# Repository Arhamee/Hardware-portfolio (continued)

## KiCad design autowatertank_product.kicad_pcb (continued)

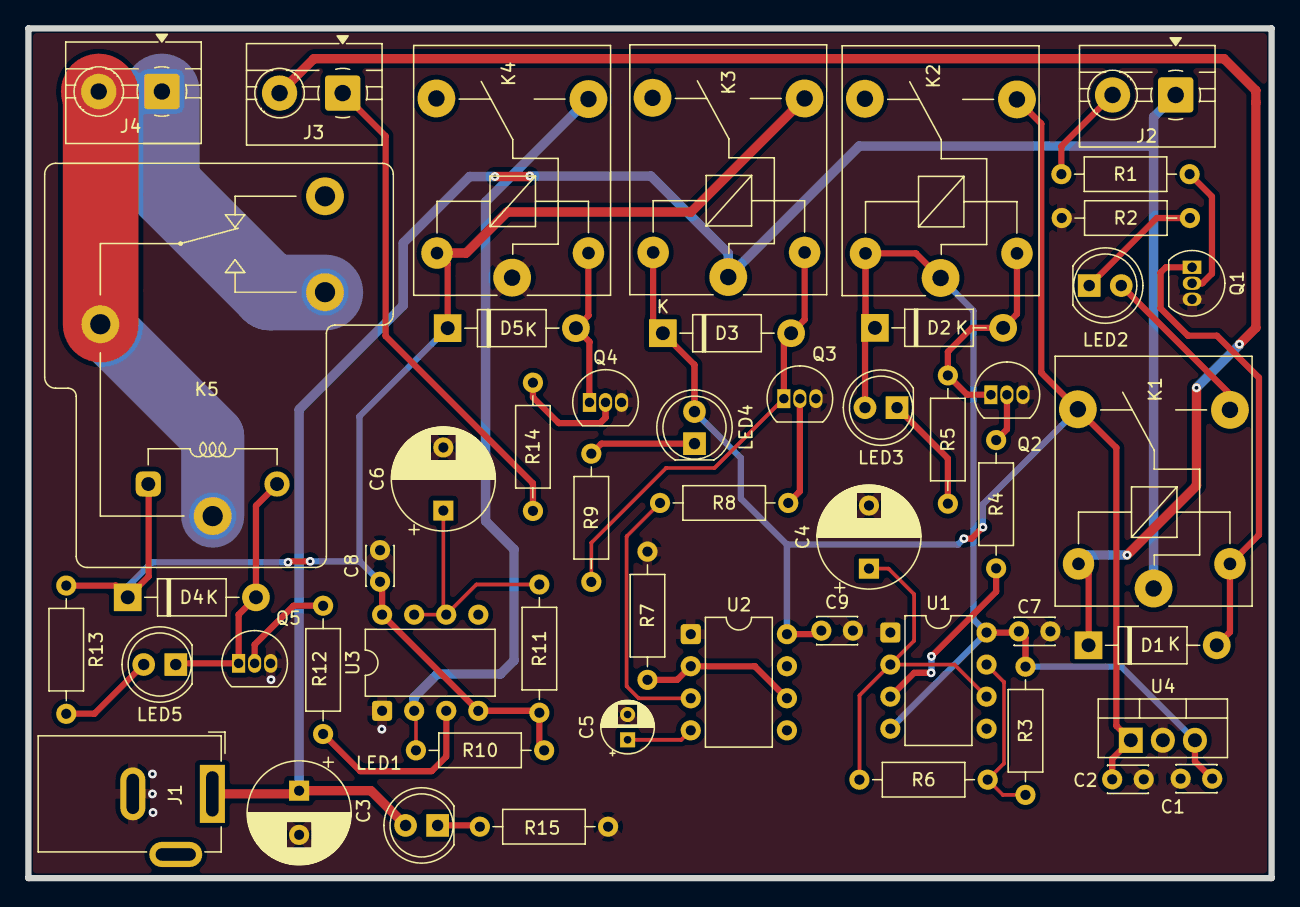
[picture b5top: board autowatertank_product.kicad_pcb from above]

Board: 2 copper layers, 98.5 x 67.3 mm, 52 parts (0 on the bottom side), 35 nets.

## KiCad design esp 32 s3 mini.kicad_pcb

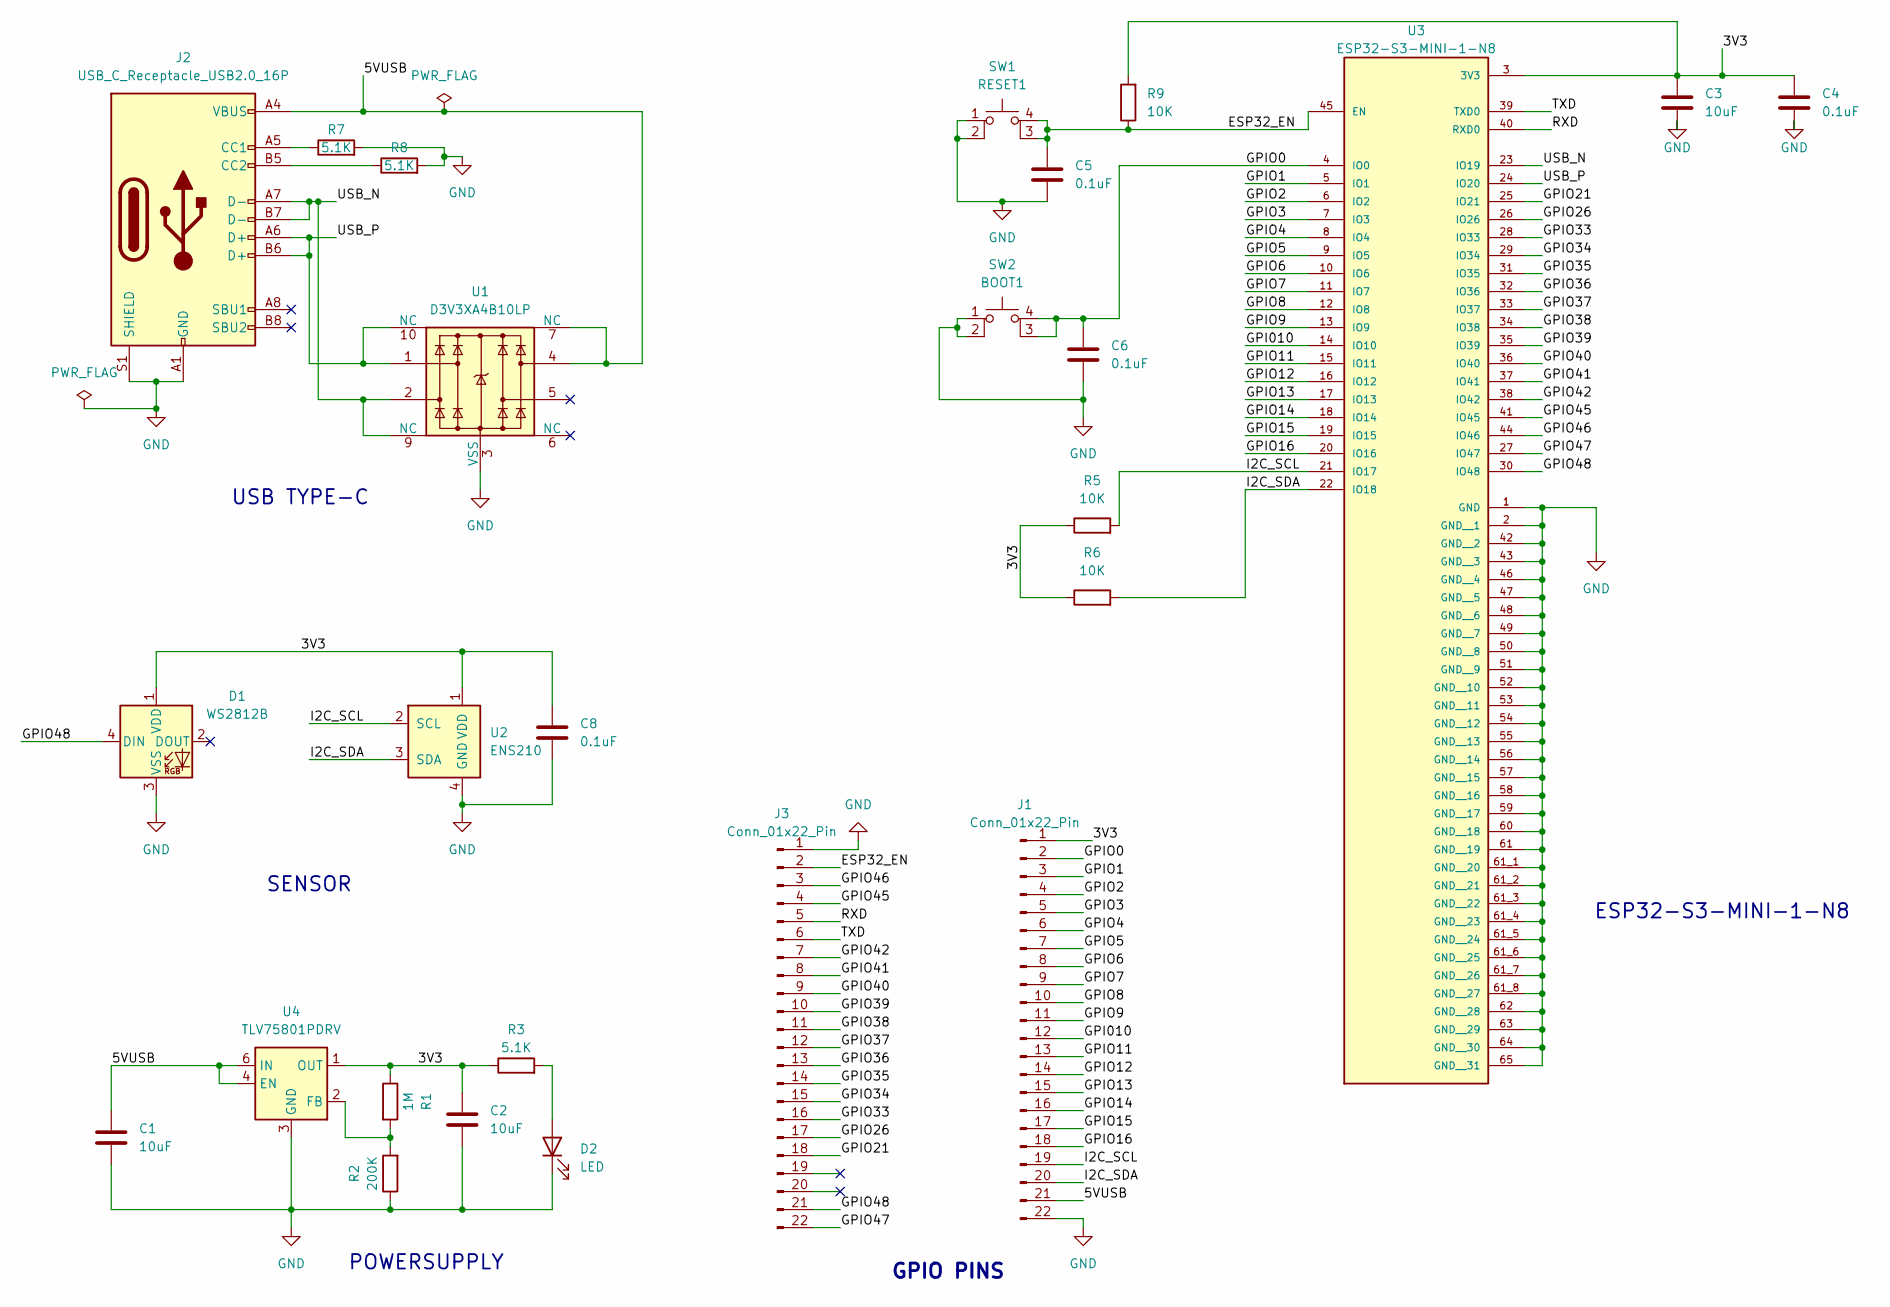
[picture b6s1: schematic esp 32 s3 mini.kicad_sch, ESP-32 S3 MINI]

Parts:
C1, C2, C3: 10uF; C_0603_1608Metric
C4, C5, C6, C8: 0.1uF; C_0603_1608Metric
D1: WS2812B; LED_WS2812B_PLCC4_5.0x5.0mm_P3.2mm
D2: LED; LED_0603_1608Metric
J1, J3: Conn_01x22_Pin; PinHeader_1x22_P2.54mm_Vertical
J2: USB_C_Receptacle_USB2.0_16P; USB_C_Receptacle_GCT_USB4105-xx-A_16P_TopMnt_Horizontal
R1: 1M; R_0603_1608Metric
R2: 200K; R_0603_1608Metric
R3, R7, R8: 5.1K; R_0603_1608Metric
R5, R6, R9: 10K; R_0603_1608Metric
SW1: RESET1; SW_SPST_PTS810
SW2: BOOT1; SW_SPST_PTS810
U1: D3V3XA4B10LP; Diodes_UDFN-10_1.0x2.5mm_P0.5mm
U2: ENS210; AMS_QFN-4-1EP_2x2mm_P0.95mm_EP0.7x1.6mm
U3: ESP32-S3-MINI-1-N8; XCVR_ESP32-S3-MINI-1-N8; PARTREV v0.6
U4: TLV75801PDRV; WSON-6-1EP_2x2mm_P0.65mm_EP1x1.6mm

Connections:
/3V3: C2.1, C3.1, C4.1, C8.1, D1.1 (VDD), J1.1, R1.1, R3.1, R5.1, R6.1, R9.2, U2.1 (VDD), U3.3 (3V3), U4.1 (OUT)
/5VUSB: C1.1, J1.21, J2.A4 (VBUS), J2.A9 (VBUS), J2.B4 (VBUS), J2.B9 (VBUS), U1.4, U1.7 (NC), U4.4 (EN), U4.6 (IN)
/ESP32_EN: C5.1, J3.2, R9.1, SW1.3 (K), SW1.4 (A), U3.45 (EN)
/GPI010: J1.12, U3.14 (IO10)
/GPIO0: C6.1, J1.2, SW2.3 (K), SW2.4 (A), U3.4 (IO0)
/GPIO1: J1.3, U3.5 (IO1)
/GPIO2: J1.4, U3.6 (IO2)
/GPIO3: J1.5, U3.7 (IO3)
/GPIO4: J1.6, U3.8 (IO4)
/GPIO5: J1.7, U3.9 (IO5)
/GPIO6: J1.8, U3.10 (IO6)
/GPIO7: J1.9, U3.11 (IO7)
/GPIO8: J1.10, U3.12 (IO8)
/GPIO9: J1.11, U3.13 (IO9)
/GPIO11: J1.13, U3.15 (IO11)
/GPIO12: J1.14, U3.16 (IO12)
/GPIO13: J1.15, U3.17 (IO13)
/GPIO14: J1.16, U3.18 (IO14)
/GPIO15: J1.17, U3.19 (IO15)
/GPIO16: J1.18, U3.20 (IO16)
/GPIO21: J3.18, U3.25 (IO21)
/GPIO26: J3.17, U3.26 (IO26)
/GPIO33: J3.16, U3.28 (IO33)
/GPIO34: J3.15, U3.29 (IO34)
/GPIO35: J3.14, U3.31 (IO35)
/GPIO36: J3.13, U3.32 (IO36)
/GPIO37: J3.12, U3.33 (IO37)
/GPIO38: J3.11, U3.34 (IO38)
/GPIO39: J3.10, U3.35 (IO39)
/GPIO40: J3.9, U3.36 (IO40)
/GPIO41: J3.8, U3.37 (IO41)
/GPIO42: J3.7, U3.38 (IO42)
/GPIO45: J3.4, U3.41 (IO45)
/GPIO46: J3.3, U3.44 (IO46)
/GPIO47: J3.22, U3.27 (IO47)
/GPIO48: D1.4 (DIN), J3.21, U3.30 (IO48)
/I2C_SCL: J1.19, R5.2, U2.2 (SCL), U3.21 (IO17)
/I2C_SDA: J1.20, R6.2, U2.3 (SDA), U3.22 (IO18)
/RXD: J3.5, U3.40 (RXD0)
/TXD: J3.6, U3.39 (TXD0)
/USB_N: J2.A7 (D-), J2.B7 (D-), U1.2, U1.9 (NC), U3.23 (IO19)
/USB_P: J2.A6 (D+), J2.B6 (D+), U1.1, U1.10 (NC), U3.24 (IO20)
GND: C1.2, C2.2, C3.2, C4.2, C5.2, C6.2, C8.2, D1.3 (VSS), D2.1 (K), J1.22, J2.A1 (GND), J2.A12 (GND), J2.B1 (GND), J2.B12 (GND), J2.S1 (SHIELD), J3.1, R2.1, R7.2, R8.2, SW1.1, SW1.2, SW2.1, SW2.2, U1.3 (VSS), U1.8 (VSS), U2.4 (GND), U2.5 (GND), U3.1 (GND), U3.2 (GND__1), U3.42 (GND__2), U3.43 (GND__3), U3.46 (GND__4), U3.47 (GND__5), U3.48 (GND__6), U3.49 (GND__7), U3.50 (GND__8), U3.51 (GND__9), U3.52 (GND__10), U3.53 (GND__11), U3.54 (GND__12), U3.55 (GND__13), U3.56 (GND__14), U3.57 (GND__15), U3.58 (GND__16), U3.59 (GND__17), U3.60 (GND__18), U3.61 (GND__19), U3.61_1 (GND__20), U3.61_2 (GND__21), U3.61_3 (GND__22), U3.61_4 (GND__23), U3.61_5 (GND__24), U3.61_6 (GND__25), U3.61_7 (GND__26), U3.61_8 (GND__27), U3.62 (GND__28), U3.63 (GND__29), U3.64 (GND__30), U3.65 (GND__31), U4.3 (GND), U4.7 (GND)
unnamed: D2.2 (A), R3.2
unnamed: J2.A5 (CC1), R7.1
unnamed: J2.B5 (CC2), R8.1
unnamed: R1.2, R2.2, U4.2 (FB)

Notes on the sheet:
GPIO PINS
POWERSUPPLY
SENSOR
USB TYPE-C
ESP32-S3-MINI-1-N8

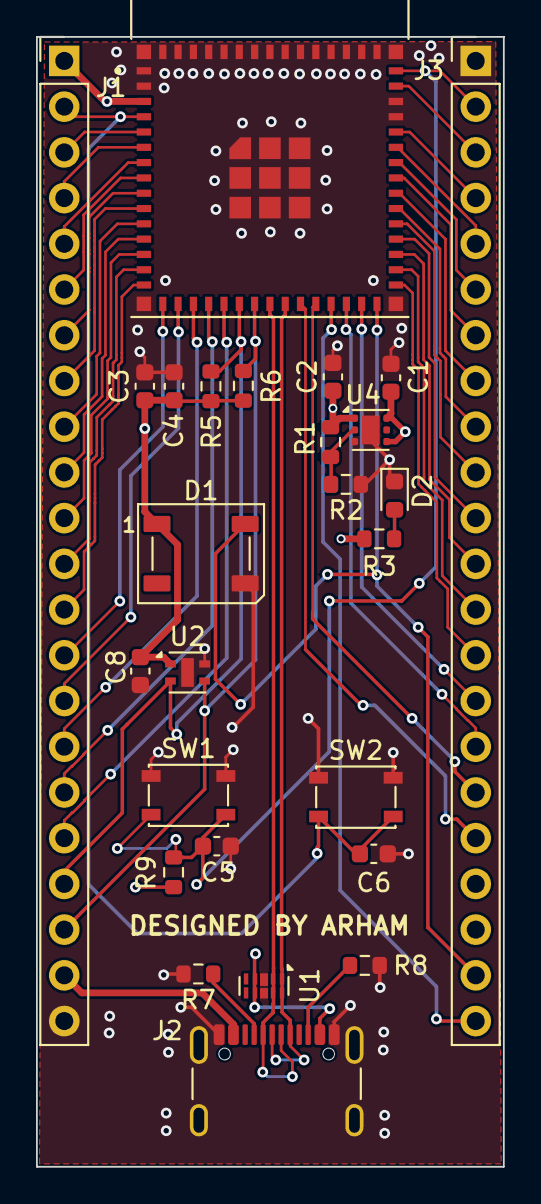
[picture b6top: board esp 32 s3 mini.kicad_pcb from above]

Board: 4 copper layers, 25.9 x 62.8 mm, 26 parts (0 on the bottom side), 47 nets.

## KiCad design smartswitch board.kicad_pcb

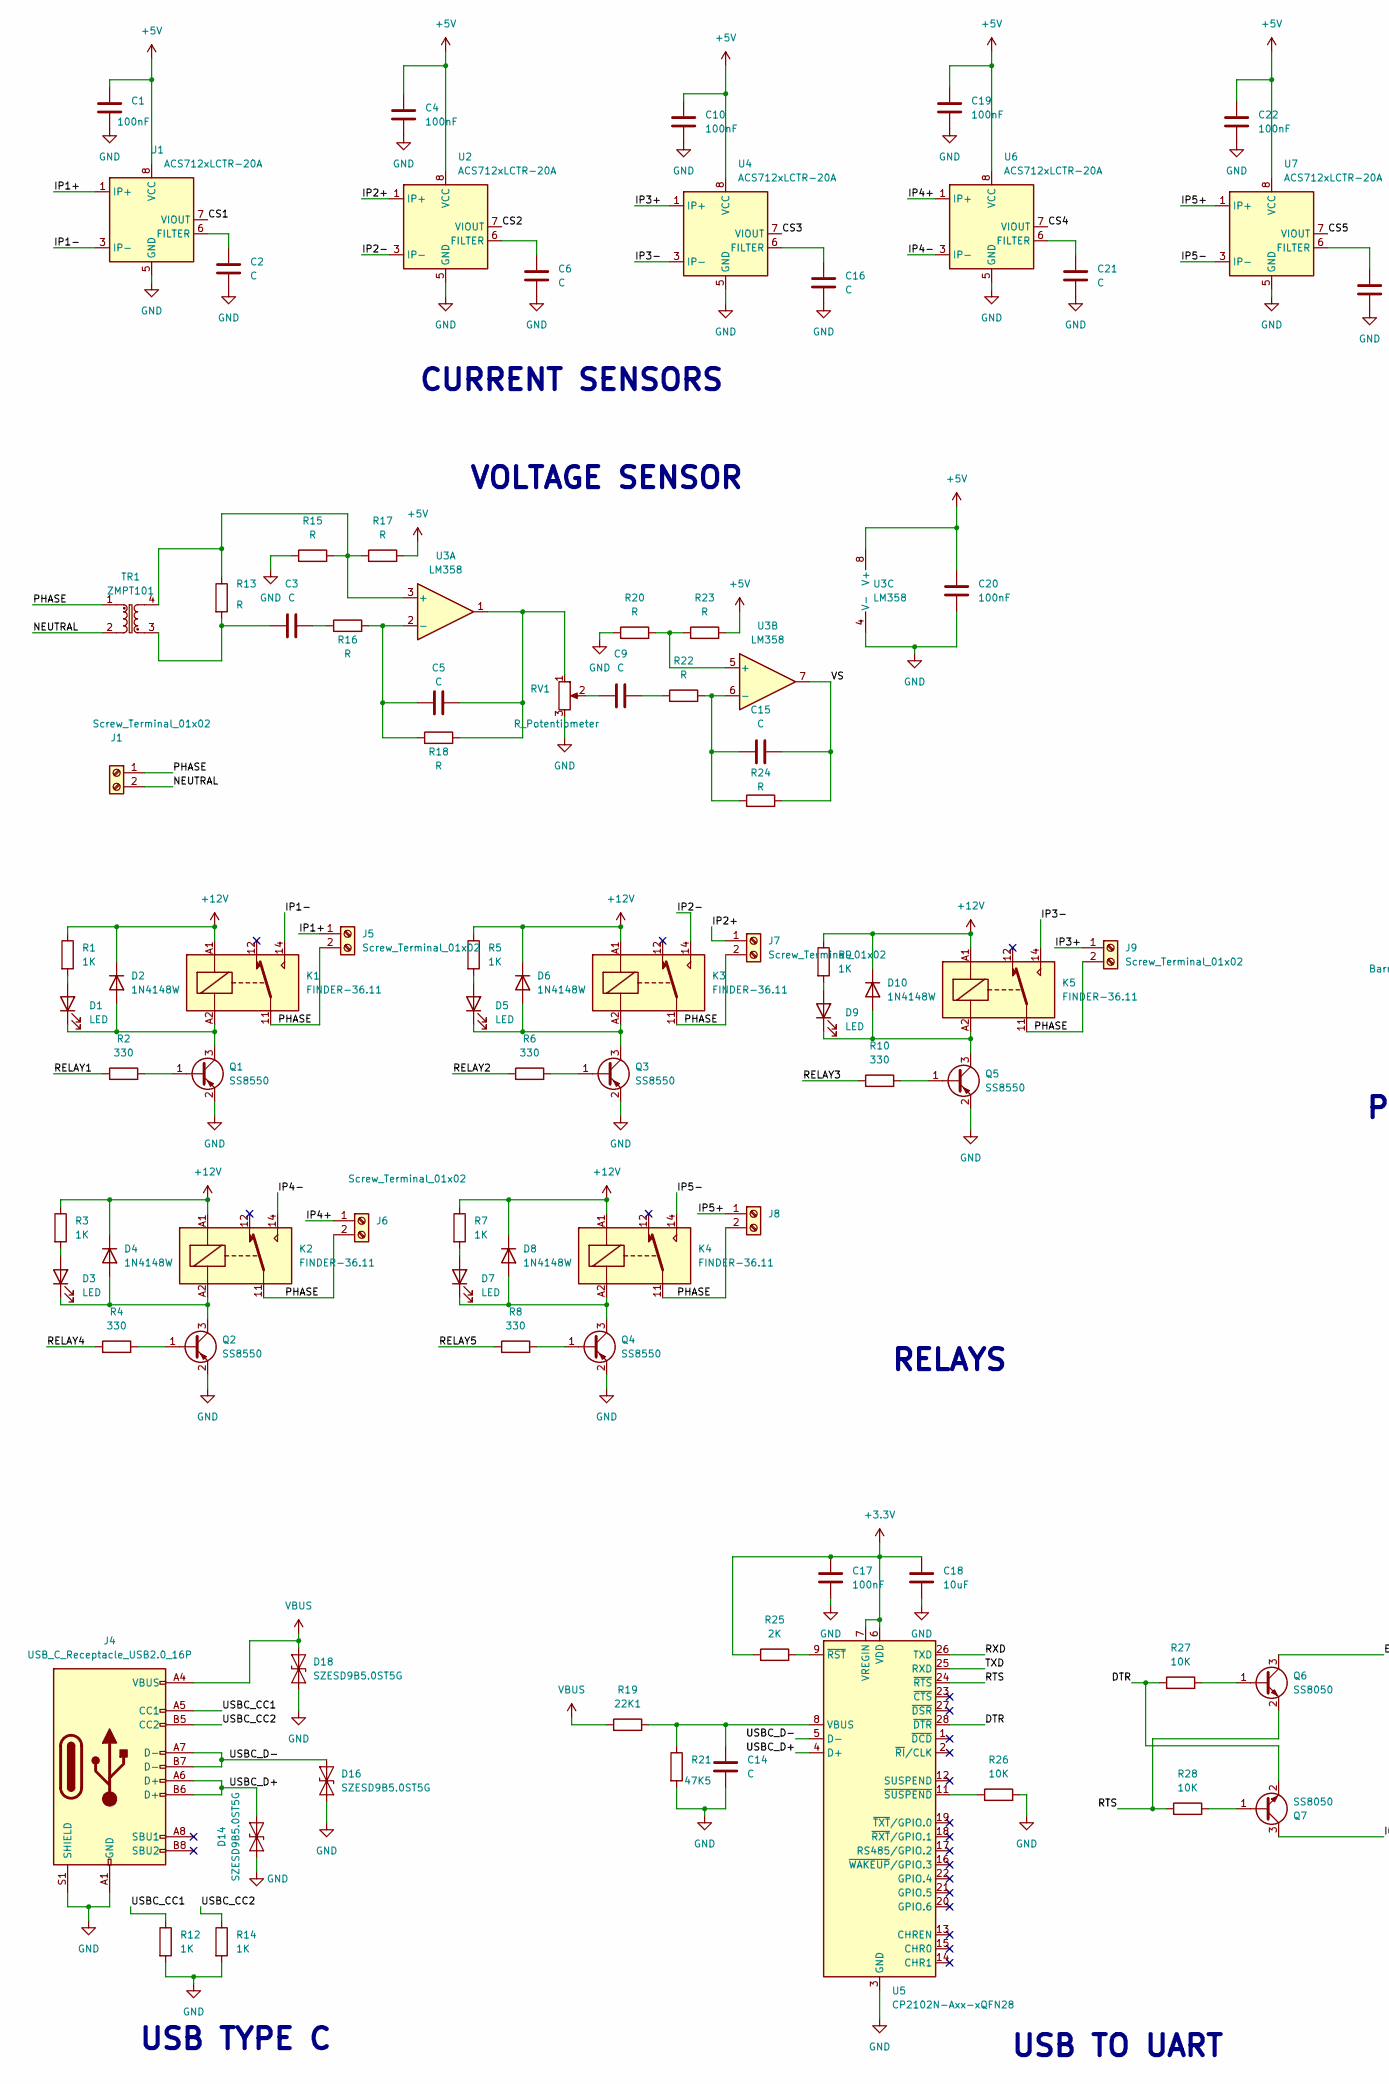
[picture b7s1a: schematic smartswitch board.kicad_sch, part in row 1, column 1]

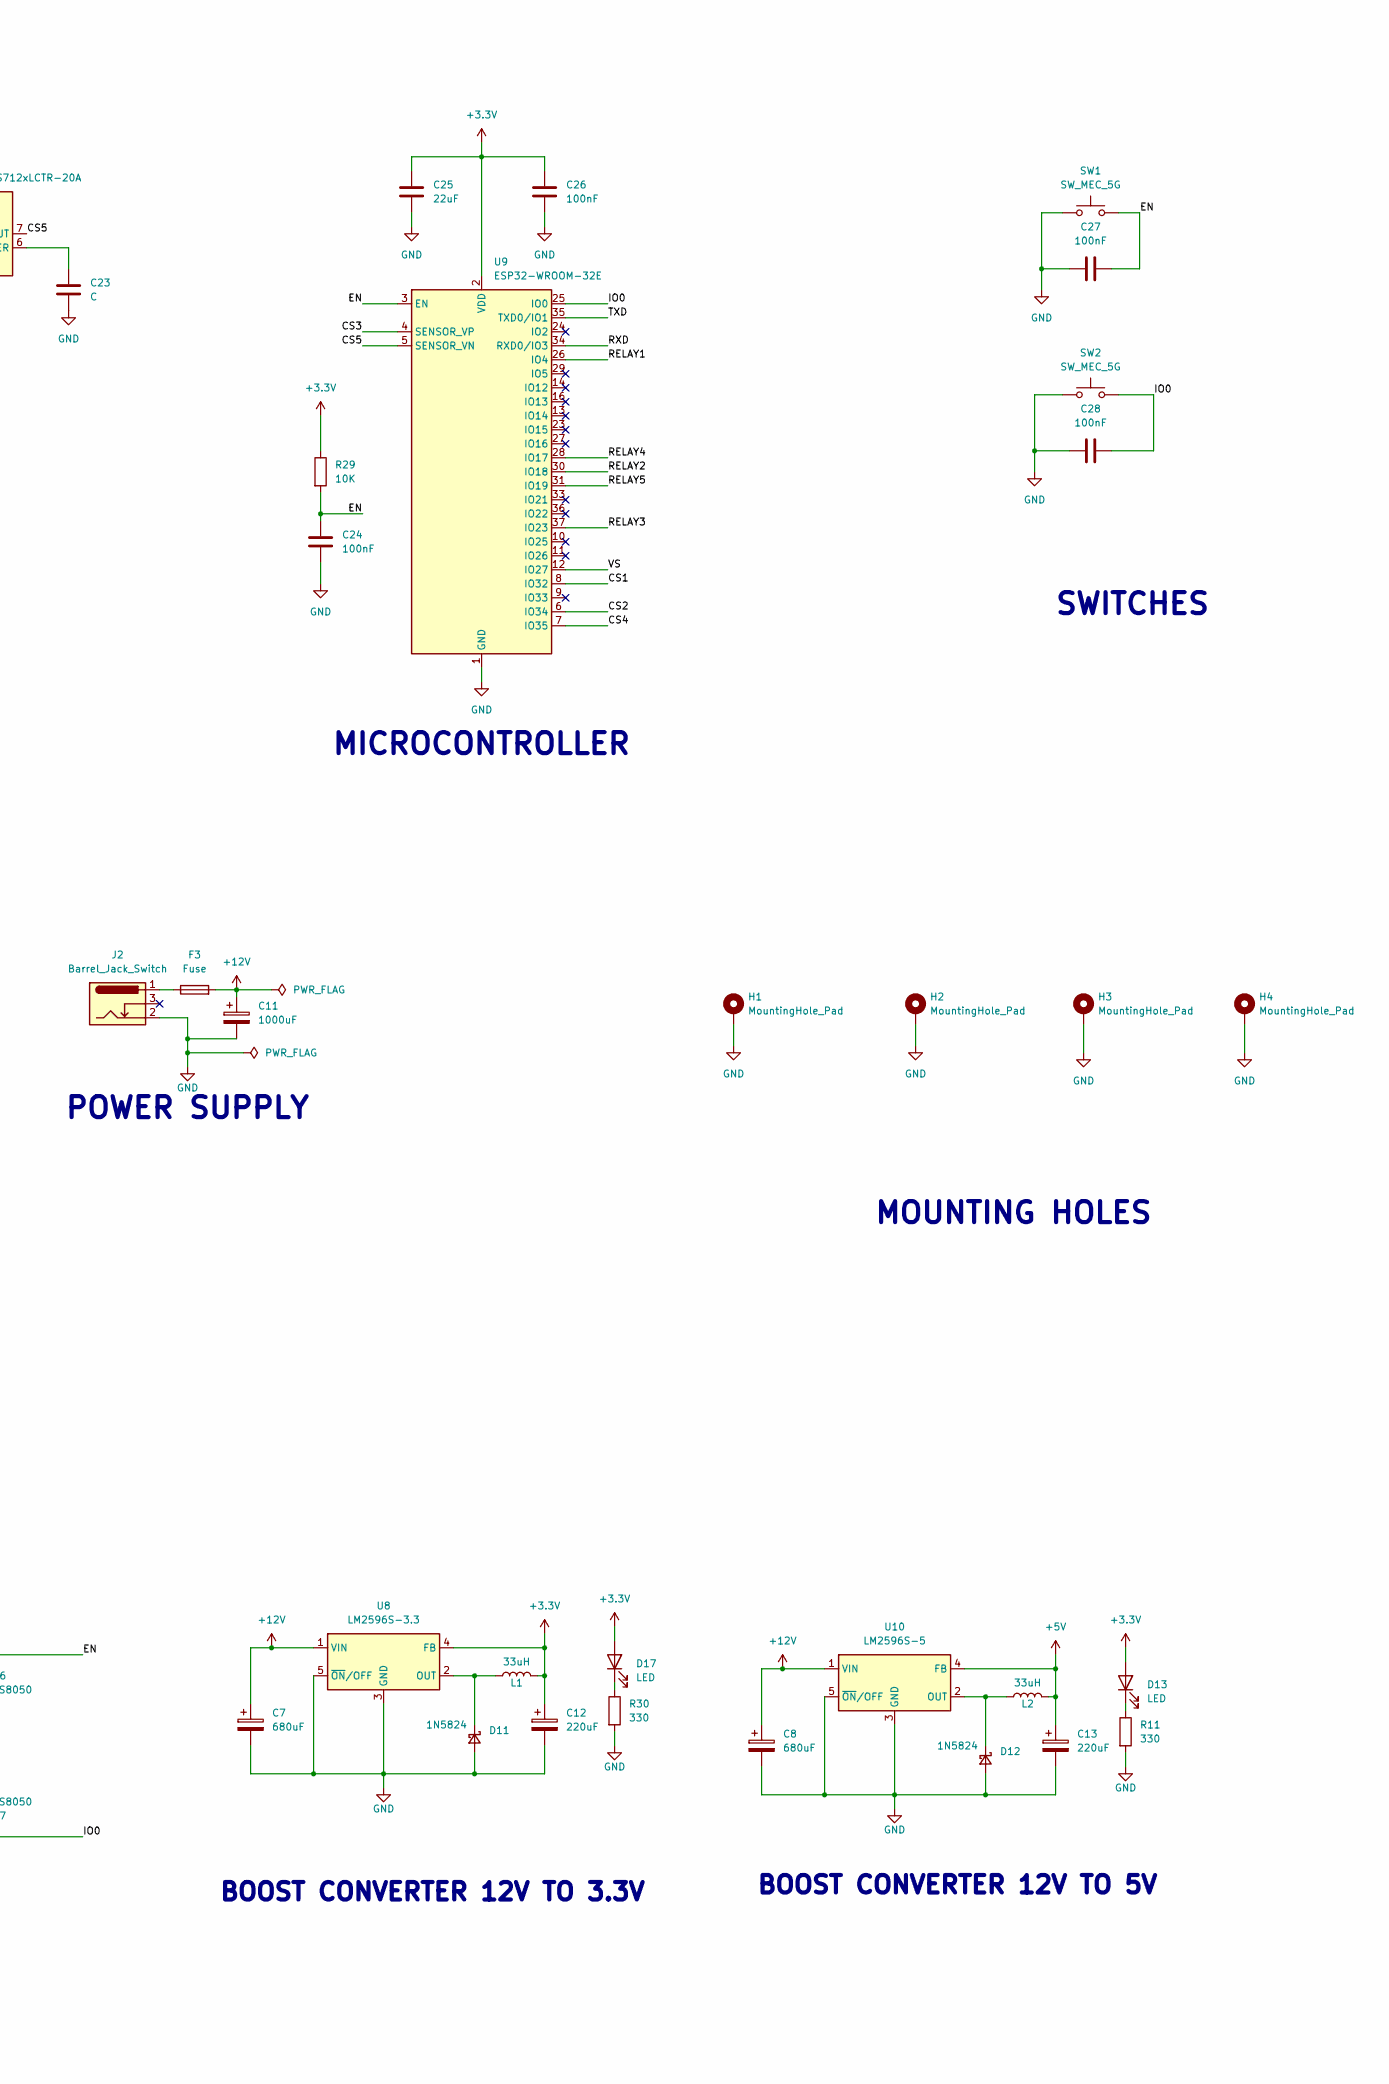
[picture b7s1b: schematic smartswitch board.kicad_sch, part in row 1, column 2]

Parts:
C1, C4, C10, C17, C19, C20, C22, C24, C26, C27, C28: 100nF; C_0402_1005Metric_Pad0.74x0.62mm_HandSolder
C2, C3, C5, C6, C9, C14, C15, C16, C23: C; C_0402_1005Metric_Pad0.74x0.62mm_HandSolder
C7, C8: 680uF; CP_Radial_D7.5mm_P2.50mm
C11: 1000uF; CP_Radial_D8.0mm_P3.50mm
C12, C13: 220uF; CP_Radial_D6.3mm_P2.50mm
C18: 10uF; C_0603_1608Metric_Pad1.08x0.95mm_HandSolder
C21: C; C_0603_1608Metric_Pad1.08x0.95mm_HandSolder
C25: 22uF; C_0603_1608Metric_Pad1.08x0.95mm_HandSolder
D1, D3, D5: LED; C_0402_1005Metric_Pad0.74x0.62mm_HandSolder
D2, D4, D6, D8, D10: 1N4148W; D_SOD-123
D7, D9, D13, D17: LED; LED_0402_1005Metric_Pad0.77x0.64mm_HandSolder
D11, D12: 1N5824; D_0603_1608Metric_Pad1.05x0.95mm_HandSolder
D14, D16, D18: SZESD9B5.0ST5G; D_SOD-923
F3: Fuse; Fuse_1210_3225Metric_Pad1.42x2.65mm_HandSolder
H1, H2, H3, H4: MountingHole_Pad; MountingHole_2.2mm_M2_DIN965_Pad
J1, J5, J6, J7, J8, J9: Screw_Terminal_01x02; TerminalBlock_Phoenix_MKDS-1,5-2_1x02_P5.00mm_Horizontal
J2: Barrel_Jack_Switch; BarrelJack_Horizontal
J4: USB_C_Receptacle_USB2.0_16P; USB_C_Receptacle_GCT_USB4105-xx-A_16P_TopMnt_Horizontal
K1, K2, K3, K4, K5: FINDER-36.11; Relay_SPDT_Finder_36.11
L1, L2: 33uH; L_Changjiang_FNR4015S
Q1, Q2, Q3, Q4, Q5: SS8550; SOT-23
Q6, Q7: SS8050; SOT-23
R1, R3, R5, R7, R9, R12, R14: 1K; R_0603_1608Metric_Pad0.98x0.95mm_HandSolder
R2, R4, R6, R8, R10, R11, R30: 330; R_0603_1608Metric_Pad0.98x0.95mm_HandSolder
R13, R15, R16, R17, R18, R20, R22, R23, R24: R; R_0603_1608Metric_Pad0.98x0.95mm_HandSolder
R19: 22K1; R_0603_1608Metric_Pad0.98x0.95mm_HandSolder
R21: 47K5; R_0603_1608Metric_Pad0.98x0.95mm_HandSolder
R25: 2K; R_0603_1608Metric_Pad0.98x0.95mm_HandSolder
R26, R27, R28, R29: 10K; R_0603_1608Metric_Pad0.98x0.95mm_HandSolder
RV1: R_Potentiometer; Potentiometer_Bourns_3296W_Vertical
SW1, SW2: SW_MEC_5G; PTS645S_SMTR92_CNK
TR1: ZMPT101; Transformer_Zeming_ZMPT101K
U1, U2, U4, U6, U7: ACS712xLCTR-20A; SOIC-8_3.9x4.9mm_P1.27mm
U3: LM358; SOIC-8_3.9x4.9mm_P1.27mm
U5: CP2102N-Axx-xQFN28; QFN-28-1EP_5x5mm_P0.5mm_EP3.35x3.35mm
U8: LM2596S-3.3; TO-263-5_TabPin3
U9: ESP32-WROOM-32E; ESP32-WROOM-32D
U10: LM2596S-5; TO-263-5_TabPin3

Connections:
+3.3V: C12.1, C17.1, C18.1, C25.1, C26.1, D13.2 (A), D17.2 (A), L1.2, R25.1, R29.1, U5.6 (VDD), U5.7 (VREGIN), U8.4 (FB), U9.2 (VDD)
+5V: C1.1, C4.1, C10.1, C13.1, C19.1, C20.2, C22.1, L2.2, R17.2, R23.2, U1.8 (VCC), U2.8 (VCC), U3.8 (V+), U4.8 (VCC), U6.8 (VCC), U7.8 (VCC), U10.4 (FB)
+12V: C7.1, C8.1, C11.1, D2.1 (K), D4.1 (K), D6.1 (K), D8.1 (K), D10.1 (K), F3.2, K1.A1, K2.A1, K3.A1, K4.A1, K5.A1, R1.1, R3.1, R5.1, R7.1, R9.1, U8.1 (VIN), U10.1 (VIN)
/CS1: U1.7 (VIOUT), U9.8 (IO32)
/CS2: U2.7 (VIOUT), U9.6 (IO34)
/CS3: U4.7 (VIOUT), U9.4 (SENSOR_VP)
/CS4: U6.7 (VIOUT), U9.7 (IO35)
/CS5: U7.7 (VIOUT), U9.5 (SENSOR_VN)
/DTR: Q7.2 (E), R27.1, U5.28 (~DTR)
/EN: C24.1, C27.1, Q6.3 (C), R29.2, SW1.3 (B), SW1.4 (B), U9.3 (EN)
/IO0: C28.2, Q7.3 (C), SW2.3 (B), SW2.4 (B), U9.25 (IO0)
/IP1+: J5.1, U1.1 (IP+), U1.2 (IP+)
/IP1-: K1.14, U1.3 (IP-), U1.4 (IP-)
/IP2+: J7.1, U2.1 (IP+), U2.2 (IP+)
/IP2-: K3.14, U2.3 (IP-), U2.4 (IP-)
/IP3+: J9.1, U4.1 (IP+), U4.2 (IP+)
/IP3-: K5.14, U4.3 (IP-), U4.4 (IP-)
/IP4+: J6.1, U6.1 (IP+), U6.2 (IP+)
/IP4-: K2.14, U6.3 (IP-), U6.4 (IP-)
/IP5+: J8.1, U7.1 (IP+), U7.2 (IP+)
/IP5-: K4.14, U7.3 (IP-), U7.4 (IP-)
/NEUTRAL: J1.2, TR1.2
/PHASE: J1.1, J5.2, J6.2, J7.2, J8.2, J9.2, K1.11, K2.11, K3.11, K4.11, K5.11, TR1.1
/RELAY1: R2.1, U9.26 (IO4)
/RELAY2: R6.1, U9.30 (IO18)
/RELAY3: R10.1, U9.37 (IO23)
/RELAY4: R4.1, U9.28 (IO17)
/RELAY5: R8.1, U9.31 (IO19)
/RTS: Q6.2 (E), R28.1, U5.24 (~RTS)
/RXD: U5.26 (TXD), U9.34 (RXD0/IO3)
/TXD: U5.25 (RXD), U9.35 (TXD0/IO1)
/USBC_CC1: J4.A5 (CC1), R12.1
/USBC_CC2: J4.B5 (CC2), R14.1
/USBC_D+: D14.2 (A2), J4.A6 (D+), J4.B6 (D+), U5.4 (D+)
/USBC_D-: D16.2 (A2), J4.A7 (D-), J4.B7 (D-), U5.5 (D-)
/VS: C15.2, R24.2, U3.7, U9.12 (IO27)
GND: C1.2, C2.2, C4.2, C6.2, C7.2, C8.2, C10.2, C11.2, C12.2, C13.2, C14.2, C16.2, C17.2, C18.2, C19.2, C20.1, C21.2, C22.2, C23.2, C24.2, C25.2, C26.2, C27.2, C28.1, D11.2 (A), D12.2 (A), D14.1 (A1), D16.1 (A1), D18.1 (A1), H1.1, H2.1, H3.1, H4.1, J2.2, J4.A1 (GND), J4.A12 (GND), J4.B1 (GND), J4.B12 (GND), J4.S1 (SHIELD), Q1.2 (E), Q2.2 (E), Q3.2 (E), Q4.2 (E), Q5.2 (E), R11.2, R12.2, R14.2, R15.1, R20.1, R21.2, R26.2, R30.2, RV1.3, SW1.1 (A), SW1.2 (A), SW2.1 (A), SW2.2 (A), U1.5 (GND), U2.5 (GND), U3.4 (V-), U4.5 (GND), U5.3 (GND), U5.29 (GND), U6.5 (GND), U7.5 (GND), U8.3 (GND), U8.5 (~ON/OFF), U9.1 (GND), U9.15 (GND), U9.38 (GND), U9.39 (GND), U10.3 (GND), U10.5 (~ON/OFF)
unnamed: C3.1, R13.2, TR1.3
unnamed: C3.2, R16.1
unnamed: C5.2, R18.2, RV1.1, U3.1
unnamed: C9.1, RV1.2
unnamed: C9.2, R22.1
unnamed: D1.2 (A), R1.2
unnamed: D1.1 (K), D2.2 (A), K1.A2, Q1.3 (C)
unnamed: D3.2 (A), R3.2
unnamed: D3.1 (K), D4.2 (A), K2.A2, Q2.3 (C)
unnamed: D5.2 (A), R5.2
unnamed: D5.1 (K), D6.2 (A), K3.A2, Q3.3 (C)
unnamed: D7.2 (A), R7.2
unnamed: D7.1 (K), D8.2 (A), K4.A2, Q4.3 (C)
unnamed: D9.2 (A), R9.2
unnamed: D9.1 (K), D10.2 (A), K5.A2, Q5.3 (C)
unnamed: D11.1 (K), L1.1, U8.2 (OUT)
unnamed: D12.1 (K), L2.1, U10.2 (OUT)
unnamed: D13.1 (K), R11.1
unnamed: D17.1 (K), R30.1
unnamed: F3.1, J2.1
unnamed: Q1.1 (B), R2.2
unnamed: Q2.1 (B), R4.2
unnamed: Q3.1 (B), R6.2
unnamed: Q4.1 (B), R8.2
unnamed: Q5.1 (B), R10.2
unnamed: Q6.1 (B), R27.2
unnamed: Q7.1 (B), R28.2
unnamed: C2.1, U1.6 (FILTER)
unnamed: C6.1, U2.6 (FILTER)
unnamed: R13.1, R15.2, R17.1, TR1.4, U3.3 (+)
unnamed: C5.1, R16.2, R18.1, U3.2 (-)
unnamed: R20.2, R23.1, U3.5 (+)
unnamed: C15.1, R22.2, R24.1, U3.6 (-)
unnamed: C16.1, U4.6 (FILTER)
unnamed: C14.1, R19.2, R21.1, U5.8 (VBUS)
unnamed: R25.2, U5.9 (~RST)
unnamed: R26.1, U5.11 (~SUSPEND)
unnamed: C21.1, U6.6 (FILTER)
unnamed: C23.1, U7.6 (FILTER)
VBUS: D18.2 (A2), J4.A4 (VBUS), J4.A9 (VBUS), J4.B4 (VBUS), J4.B9 (VBUS), R19.1

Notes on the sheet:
SWITCHES
USB TYPE C
USB TO UART
VOLTAGE SENSOR
POWER SUPPLY
CURRENT SENSORS
MICROCONTROLLER
RELAYS
BOOST CONVERTER 12V TO 3.3V
BOOST CONVERTER 12V TO 5V
MOUNTING HOLES

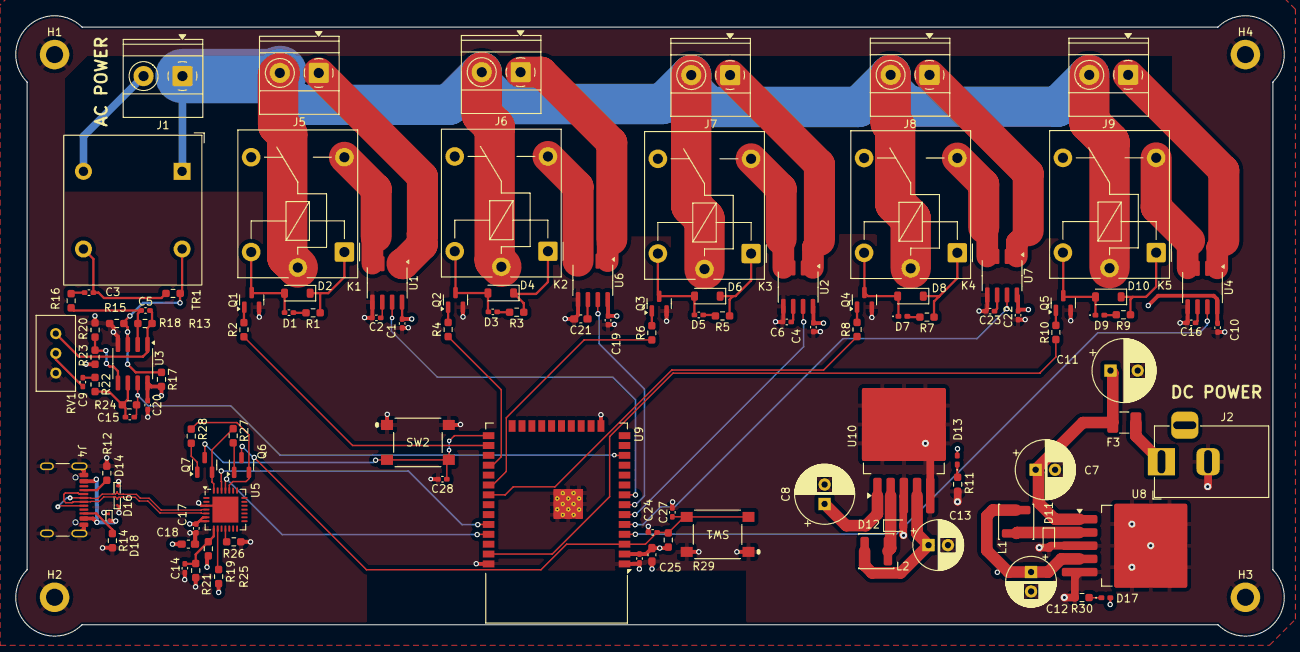
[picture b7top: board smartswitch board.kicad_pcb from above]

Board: 4 copper layers, 163.3 x 79.9 mm, 116 parts (0 on the bottom side), 77 nets.
